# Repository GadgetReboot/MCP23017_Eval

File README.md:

# MCP23017_Eval
Demo pcb for MCP23017 with 8 relays, 4 buttons, and 4 spare IO header pins

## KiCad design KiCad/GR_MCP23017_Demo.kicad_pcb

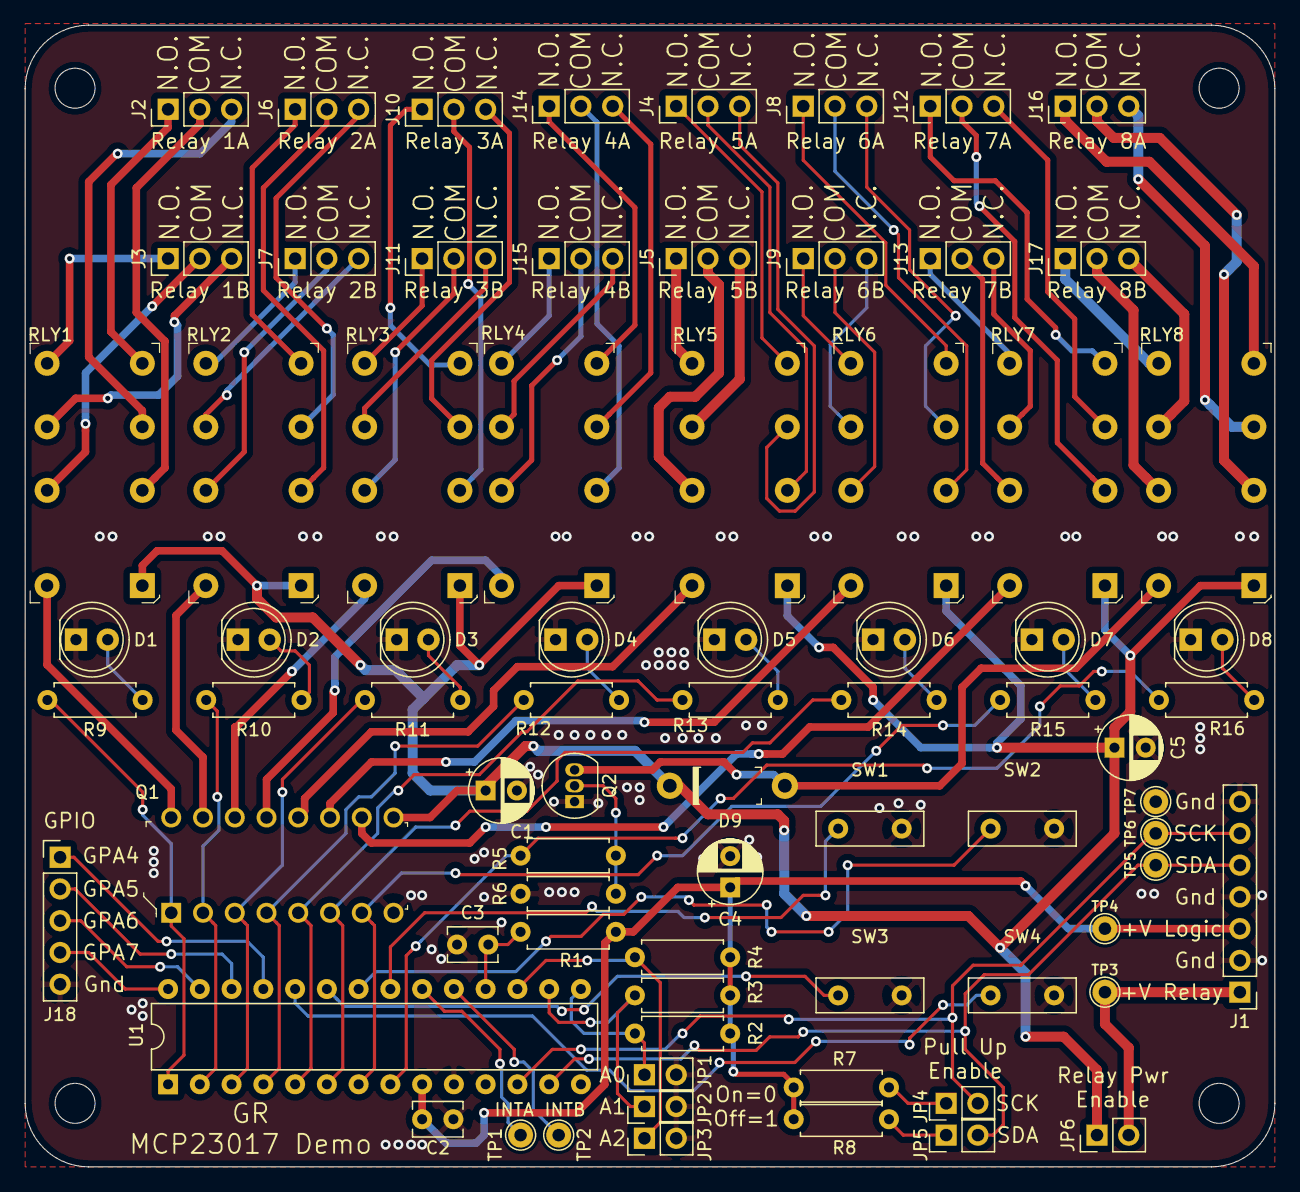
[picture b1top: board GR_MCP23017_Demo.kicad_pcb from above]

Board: 2 copper layers, 99.9 x 91.3 mm, 80 parts (0 on the bottom side), 95 nets.

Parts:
C1, C4, C5: 10uF; CP_Radial_D5.0mm_P2.50mm
C2, C3: 100nF; C_Disc_D3.8mm_W2.6mm_P2.50mm
D1, D2, D3, D4, D5, D6, D7, D8: LED_ALT; LED_D5.0mm
D9: 1N4001; DO-41
J1: Conn_01x07; PinHeader_1x07_P2.54mm_Vertical
J2, J3, J4, J5, J6, J7, J8, J9, J10, J11, J12, J13, J14, J15, J16, J17: Conn_01x03; PinHeader_1x03_P2.54mm_Vertical
J18: Conn_01x05; PinHeader_1x05_P2.54mm_Vertical
JP1, JP2, JP3, JP4, JP5, JP6: Conn_01x02; PinHeader_1x02_P2.54mm_Vertical
MH1, MH2, MH3, MH4: MountingHole; MountingHole_3.2mm_M3
Q1: ULN2003AN; DIP-16_W7.62mm
Q2: 2N3904; TO-92_Inline
R1, R2, R3, R4, R6, R7, R8: 10K; R_Axial_DIN0207_L6.3mm_D2.5mm_P7.62mm_Horizontal
R5: 1K; R_Axial_DIN0207_L6.3mm_D2.5mm_P7.62mm_Horizontal
R9, R10, R11, R12, R13, R14, R15, R16: 680r; R_Axial_DIN0207_L6.3mm_D2.5mm_P7.62mm_Horizontal
RLY1, RLY2, RLY3, RLY4, RLY5, RLY6, RLY7, RLY8: G5V-2-DC12; Relay_THT_G5V-2
SW1, SW2, SW3, SW4: SW_Push; R_Box_L8.4mm_W2.5mm_P5.08mm
TP1, TP2, TP3, TP4, TP5, TP6, TP7: TestPoint_Alt; TestPoint_THTPad_D2.0mm_Drill1.0mm
U1: MCP23017_SP; DIP-28_W7.62mm

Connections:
/A0: JP1.1, R2.2, U1.15
/A1: JP2.1, R3.2, U1.16
/A2: JP3.1, R4.2, U1.17
/COM_1a: J2.2, RLY1.4
/COM_1b: J3.2, RLY1.13
/COM_2a: J6.2, RLY2.4
/COM_2b: J7.2, RLY2.13
/COM_3a: J10.2, RLY3.4
/COM_3b: J11.2, RLY3.13
/COM_4a: J14.2, RLY4.4
/COM_4b: J15.2, RLY4.13
/COM_5a: J4.2, RLY5.4
/COM_5b: J5.2, RLY5.13
/COM_6a: J8.2, RLY6.4
/COM_6b: J9.2, RLY6.13
/COM_7a: J12.2, RLY7.4
/COM_7b: J13.2, RLY7.13
/COM_8a: J16.2, RLY8.4
/COM_8b: J17.2, RLY8.13
/GPA4: J18.1, U1.25
/GPA5: J18.2, U1.26
/GPA6: J18.3, U1.27
/GPA7: J18.4, U1.28
/NC_1a: J2.3, RLY1.6
/NC_1b: J3.3, RLY1.11
/NC_2a: J6.3, RLY2.6
/NC_2b: J7.3, RLY2.11
/NC_3a: J10.3, RLY3.6
/NC_3b: J11.3, RLY3.11
/NC_4a: J14.3, RLY4.6
/NC_4b: J15.3, RLY4.11
/NC_5a: J4.3, RLY5.6
/NC_5b: J5.3, RLY5.11
/NC_6a: J8.3, RLY6.6
/NC_6b: J9.3, RLY6.11
/NC_7a: J12.3, RLY7.6
/NC_7b: J13.3, RLY7.11
/NC_8a: J16.3, RLY8.6
/NC_8b: J17.3, RLY8.11
/NO_1a: J2.1, RLY1.8
/NO_1b: J3.1, RLY1.9
/NO_2a: J6.1, RLY2.8
/NO_2b: J7.1, RLY2.9
/NO_3a: J10.1, RLY3.8
/NO_3b: J11.1, RLY3.9
/NO_4a: J14.1, RLY4.8
/NO_4b: J15.1, RLY4.9
/NO_5a: J4.1, RLY5.8
/NO_5b: J5.1, RLY5.9
/NO_6a: J8.1, RLY6.8
/NO_6b: J9.1, RLY6.9
/NO_7a: J12.1, RLY7.8
/NO_7b: J13.1, RLY7.9
/NO_8a: J16.1, RLY8.8
/NO_8b: J17.1, RLY8.9
/Out1: Q1.1, R9.2, U1.1
/Out2: Q1.2, R10.2, U1.2
/Out3: Q1.3, R11.2, U1.3
/Out4: Q1.4, R12.2, U1.4
/Out5: Q1.5, R13.2, U1.5
/Out6: Q1.6, R14.2, U1.6
/Out7: Q1.7, R15.2, U1.7
/Out8: R5.2, R16.2, U1.8
/RLY_1_Ena: Q1.16, RLY1.16
/RLY_2_Ena: Q1.15, RLY2.16
/RLY_3_Ena: Q1.14, RLY3.16
/RLY_4_Ena: Q1.13, RLY4.16
/RLY_5_Ena: Q1.12, RLY5.16
/RLY_6_Ena: Q1.11, RLY6.16
/RLY_7_Ena: Q1.10, RLY7.16
/RLY_8_Ena: D9.A, Q2.3, RLY8.16
/SCK: J1.6, JP4.2, TP6.1, U1.12
/SDA: J1.5, JP5.2, TP5.1, U1.13
/SW1: SW1.1, U1.21
/SW2: SW2.1, U1.22
/SW3: SW3.1, U1.23
/SW4: SW4.1, U1.24
/VinRY: J1.1, JP6.2, TP3.1
GNDREF: C1.2, C2.2, C3.1, C4.2, C5.2, D1.1, D2.1, D3.1, D4.1, D5.1, D6.1, D7.1, D8.1, J1.2, J1.4, J1.7, J18.5, JP1.2, JP2.2, JP3.2, Q1.8, Q2.1, R6.2, SW1.2, SW2.2, SW3.2, SW4.2, TP7.1, U1.10
unnamed: C3.2, R1.2, U1.18
unnamed: D1.2, R9.1
unnamed: D2.2, R10.1
unnamed: D3.2, R11.1
unnamed: D4.2, R12.1
unnamed: D5.2, R13.1
unnamed: D6.2, R14.1
unnamed: D7.2, R15.1
unnamed: D8.2, R16.1
unnamed: JP4.1, R7.2
unnamed: JP5.1, R8.2
unnamed: Q2.2, R5.1, R6.1
unnamed: TP1.1, U1.20
unnamed: TP2.1, U1.19
VCC: C2.1, C4.1, J1.3, R1.1, R2.1, R3.1, R4.1, R7.1, R8.1, TP4.1, U1.9
Vdrive: C1.1, C5.1, D9.K, JP6.1, Q1.9, RLY1.1, RLY2.1, RLY3.1, RLY4.1, RLY5.1, RLY6.1, RLY7.1, RLY8.1

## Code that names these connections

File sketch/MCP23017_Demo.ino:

// MCP23017 GPIO Expander Demo
//
// Target Hardware:  Uno, MCP23017 (I2C version)
//
// Arduino to MCP23017 Connections:
// Uno Pin            MCP23017 Pin
//   SCL                  SCK
//   SDA                  SDA   
//   GND                  VSS
//    5V                  VDD
//
// MCP23017 input/output connections for demo pcb
// GPA0..GPA3 = SW1 .. SW4          push button inputs
// GPA4..GPA7 = GPA4 .. GPA7        spare header IO pins
// GPB0..GPB7 = Relay 1 .. Relay 8  outputs
//
// Arduino library pin numbers to use for MCP23017 input/output pins
// mcp23017 pin    pin name       library pin #
//     21            GPA0             0
//     22            GPA1             1
//     23            GPA2             2
//     24            GPA3             3
//     25            GPA4             4
//     26            GPA5             5
//     27            GPA6             6
//     28            GPA7             7
//      1            GPB0             8
//      2            GPB1             9
//      3            GPB2             10
//      4            GPB3             11
//      5            GPB4             12
//      6            GPB5             13
//      7            GPB6             14
//      8            GPB7             15
//
// Tested with Arduino IDE 1.8.13
// Gadget Reboot
// https://www.youtube.com/gadgetreboot

#include <Adafruit_MCP23X17.h>

#define addr 0x20     // mcp23017 address

// map mcp23017 pcb devices to gpio pin numbers used in library
#define sw1     0   // GPA0 button
#define sw2     1   // GPA1 button
#define sw3     2   // GPA2 button
#define sw4     3   // GPA3 button

#define gpa4    4   // GPA4 spare
#define gpa5    5   // GPA5 spare
#define gpa6    6   // GPA6 spare
#define gpa7    7   // GPA7 spare

#define relay1  8   // GPB0 relay
#define relay2  9   // GPB1 relay
#define relay3  10  // GPB2 relay
#define relay4  11  // GPB3 relay
#define relay5  12  // GPB4 relay
#define relay6  13  // GPB5 relay
#define relay7  14  // GPB6 relay
#define relay8  15  // GPB7 relay


Adafruit_MCP23X17 mcp;  // MCP23017 object to communicate with

void setup() {
  Serial.begin(9600);
  Serial.println("mcp23017 demo");

  // init device
  if (!mcp.begin_I2C(addr)) {
    Serial.println("Can't initialize mcp23017");
    while (1);
  }

  // configure relay pins for output
  mcp.pinMode(relay1, OUTPUT);
  mcp.pinMode(relay2, OUTPUT);
  mcp.pinMode(relay3, OUTPUT);
  mcp.pinMode(relay4, OUTPUT);
  mcp.pinMode(relay5, OUTPUT);
  mcp.pinMode(relay6, OUTPUT);
  mcp.pinMode(relay7, OUTPUT);
  mcp.pinMode(relay8, OUTPUT);

  // configure button pins for input with pull up
  mcp.pinMode(sw1, INPUT_PULLUP);
  mcp.pinMode(sw2, INPUT_PULLUP);
  mcp.pinMode(sw3, INPUT_PULLUP);
  mcp.pinMode(sw4, INPUT_PULLUP);

  // configure spare gpio pins for input with pull up
  mcp.pinMode(gpa4, INPUT_PULLUP);
  mcp.pinMode(gpa5, INPUT_PULLUP);
  mcp.pinMode(gpa6, INPUT_PULLUP);
  mcp.pinMode(gpa7, INPUT_PULLUP);

  // configure mcp pin interrupts
  // parameters:  mirroring int A/B pins, open drain output, active output polarity low/high
  // using this config, both INTA/B pins are asserted on any interrupt,
  //                    INTA/B is driven high/low and not open drain (floating)
  //                    INTA/B is active low to indicate an interrupt has occurred
  mcp.setupInterrupts(true, false, LOW);  

  // enable interrupt on sw1 changing state
  mcp.setupInterruptPin(sw1, CHANGE);

  // enable interrupt on sw2 changing state
  mcp.setupInterruptPin(sw2, CHANGE);

  // enable interrupt on sw3 changing state
  mcp.setupInterruptPin(sw3, CHANGE);

  // enable interrupt on sw4 changing state
  mcp.setupInterruptPin(sw4, CHANGE);

  // turn off relays one at a time
  mcp.digitalWrite(relay1, 0);
  mcp.digitalWrite(relay2, 0);
  mcp.digitalWrite(relay3, 0);
  mcp.digitalWrite(relay4, 0);
  mcp.digitalWrite(relay5, 0);
  mcp.digitalWrite(relay6, 0);
  mcp.digitalWrite(relay7, 0);
  mcp.digitalWrite(relay8, 0);

  // turn off relays as an entire port at once
  // mcp.writeGPIO(0x00, 1);  // set all of port B to "0"

  // relay test, cycle each relay on power up
  mcp.digitalWrite(relay1, 1);  // turn on relay 1
  delay (300);
  mcp.digitalWrite(relay1, 0);  // turn off relay 1

  mcp.digitalWrite(relay2, 1);  // turn on relay 2
  delay (300);
  mcp.digitalWrite(relay2, 0);  // turn off relay 2

  mcp.digitalWrite(relay3, 1);  // turn on relay 3
  delay (300);
  mcp.digitalWrite(relay3, 0);  // turn off relay 3

  mcp.digitalWrite(relay4, 1);  // turn on relay 4
  delay (300);
  mcp.digitalWrite(relay4, 0);  // turn off relay 4

  mcp.digitalWrite(relay5, 1);  // turn on relay 5
  delay (300);
  mcp.digitalWrite(relay5, 0);  // turn off relay 5

  mcp.digitalWrite(relay6, 1);  // turn on relay 6
  delay (300);
  mcp.digitalWrite(relay6, 0);  // turn off relay 6

  mcp.digitalWrite(relay7, 1);  // turn on relay 7
  delay (300);
  mcp.digitalWrite(relay7, 0);  // turn off relay 7

  mcp.digitalWrite(relay8, 1);  // turn on relay 8
  delay (300);
  mcp.digitalWrite(relay8, 0);  // turn off relay 8

}

void loop() {

  mcp.digitalWrite(relay1, !mcp.digitalRead(sw1));  // relay1 is on when sw1 is pressed, off when released
  mcp.digitalWrite(relay2, !mcp.digitalRead(sw2));  // relay2 is on when sw2 is pressed, off when released
  mcp.digitalWrite(relay3, !mcp.digitalRead(sw3));  // relay3 is on when sw3 is pressed, off when released
  mcp.digitalWrite(relay4, !mcp.digitalRead(sw4));  // relay4 is on when sw4 is pressed, off when released

  mcp.digitalWrite(relay5, !mcp.digitalRead(gpa4));  // relay5 is on when gpa4 is low, off when high/open
  mcp.digitalWrite(relay6, !mcp.digitalRead(gpa5));  // relay6 is on when gpa5 is low, off when high/open
  mcp.digitalWrite(relay7, !mcp.digitalRead(gpa6));  // relay7 is on when gpa6 is low, off when high/open
  mcp.digitalWrite(relay8, !mcp.digitalRead(gpa7));  // relay8 is on when gpa7 is low, off when high/open

  // force all relays on for 1 second and then off, if gpa4 goes low
  if (!mcp.digitalRead(gpa4)) {
    mcp.writeGPIO(0xff, 1);  // turn on all relays if gpa4 is low (write 0xff to port b)
    delay (1000);            // wait 1 second
    mcp.writeGPIO(0x00, 1);  // turn off all relays (write 0x00 to port b)
  }

  /*
      //more port read/write examples
      //read port A or port B into a byte
      byte test = mcp.readGPIO(0); // read port A =0 B =1

      //write a byte to port A or port B
      mcp.writeGPIO(test, 1);  // write byte to port A =0 B =1

      // read or write both ports as 16 bits all at once
      uint16_t data16 = mcp.readGPIOAB();  // read both ports into uint16_t
      mcp.writeGPIOAB(data16);             // write both ports from uint16_t
  */


}
